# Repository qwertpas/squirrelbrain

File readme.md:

## Squirrelbrain v2

[Youtube video](https://youtube.com/shorts/pgTb6q6fkRE?feature=shared)

Main control board for the [Pintobotics](https://pintobotics.substack.com) robotic squirrel. It uses a Seeeduino XIAO ESP32S3 for wireless communication with a base station, is able to drive [dynamixel 5V TTL servos](https://www.robotis.us/dynamixel-xl330-m077-t/) up to 6A, and has two separate RS485 buses. 

The RS485 buses are intended for:
* [Ø32controller](https://github.com/qwertpas/O32controller), a miniature closed-loop brushless motor driver
* [Ø12encoder](https://github.com/qwertpas/O12encoder), a miniature magnetic encoder (MA702)
* [Ø12imu](https://github.com/qwertpas/O12imu), a miniature IMU with built-in sensor fusion for orientation (LSM6DSV) 

Squirrelbrain has two load switches to allow the ESP32 to cut off power to the motors when the battery is still connected. One load switch operates an XT30 output, featuring current sensing and a programmed current limit of 38A (limit can be adjusted by replacing a resistor). The other load switch operates on the 5V supply intended for dynamixel servos.

Size: 27mm x 27mm

Mounting: 4x M2 on 32mm diameter circle 

Connections:
* 2x JST-SH 2pin connectors for RS485 communication (1 for each bus)
* 2x 4pin 0.5mm pitch double-sided FFC connectors for RS485 communication (1 for each bus)
* 2x solder pads for 3.3V output
* JST-EH 3pin connector for dynamixel TTL
* USB-C on the ESP32S3
* Optional camera module on the ESP32S3
* XT30U-M power in (5-15V)
* XT30U-F power out
* 4pin header for current sense output, extra GPIO, and 5V/GND output

#### Changelog from Squirrelbrain v1:
Squirrelbrain v1 does not have the FFC connectors and is missing a pullup on the dynamixel data line.

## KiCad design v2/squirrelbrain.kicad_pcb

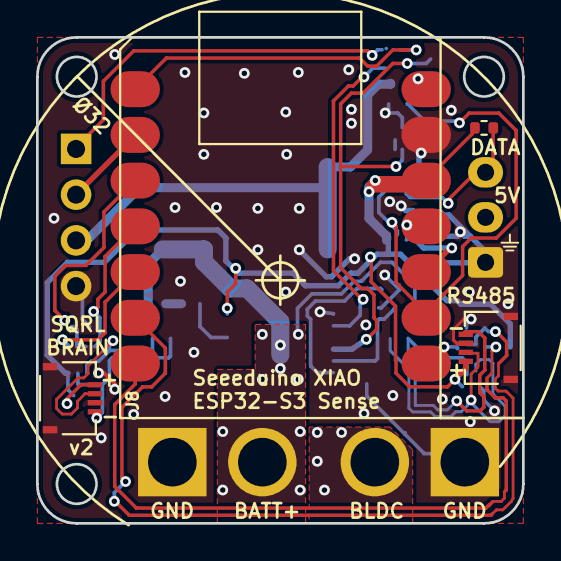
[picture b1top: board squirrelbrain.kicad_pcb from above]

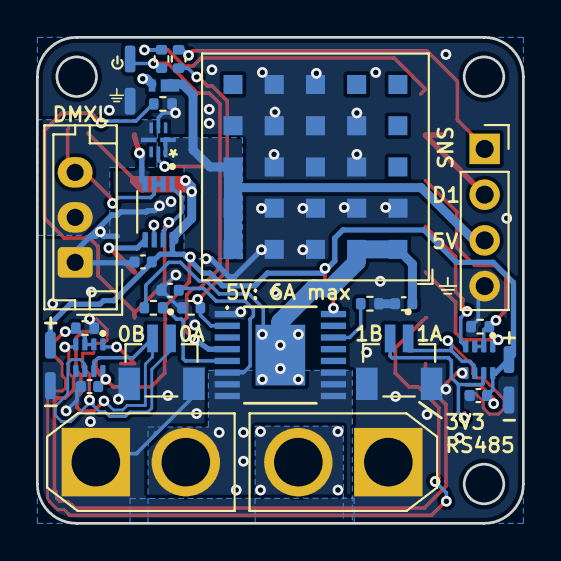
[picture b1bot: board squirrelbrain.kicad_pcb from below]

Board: 2 copper layers, 27.0 x 27.0 mm, 36 parts (32 on the bottom side), 28 nets.

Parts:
C1, C2, C3, C4, C5: 100nF; C_0402_1005Metric
D1: SDM2U30CSP; SDM2U30CSP-7
J1, J3: BM02B-SRSS-TB_LF__SN_; JST_BM02B-SRSS-TB_LF__SN_
J2: Conn_01x03; JST_EH_B3B-EH-A_1x03_P2.50mm_Vertical
J4: BATT; AMASS_XT30U-M_1x02_P5.0mm_Vertical
J5: BLDC_PWR; AMASS_XT30U-F_1x02_P5.0mm_Vertical
J6: GPIO1; PinSocket_1x04_P2.54mm_Vertical
J7, J8: Conn_01x04; TE_2328702-4
R1: 390R; R_0402_1005Metric
R2, R3, R4, R5, R6, R7, R8: 10k; R_0402_1005Metric
R9: 1k; R_0402_1005Metric
TP1, TP2, TP3, TP4, TP5, TP6: TestPoint; TestPoint_Pad_Rect
U1: RPM5.0-6.0; Converter_DCDC_RECOM_RPMx.x-x.0
U2: TPS1HB08BQPWPRQ1; TPS1HB08
U3: TPS22992SRXNR; TPS22992S
U4: SEEEDUINO-XIAO-ESP32S3; XIAO-ESP32S3-2.54-21X17.8MM
U5, U7: THVD1420DRLR; THVD1420DRLR_SOT-585
U6: SN74LVC2G241DCUR; SN74LVC2G125DCU

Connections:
+3V3: C3.1, C4.1, C5.1, J7.4, J8.4, R4.2, TP2.1, TP4.1, U2.16 (DIA_EN), U4.12 (3V3), U5.8 (VCC), U6.8 (VCC), U7.8 (VCC)
+5V: D1.2 (A), J6.3, U1.A5 (+VOUT), U1.B5 (+VOUT), U1.C5 (Sense), U3.1 (VBIAS), U3.2 (VIN)
+5VP: J2.2, U3.5 (QOD), U3.6 (VOUT)
+BATT: C1.1, J4.2, R3.2, U1.A1 (+VIN), U1.A2 (+VIN), U2.EPAD (VBB)
/5V_ESP: D1.1 (K), U4.14 (5V)
/BLDC_PWR: C2.1, J5.2, U2.6 (VOUT), U2.7 (VOUT), U2.8 (VOUT), U2.9 (VOUT), U2.10 (VOUT), U2.11 (VOUT)
/DMXL_DATA: J2.3, R4.1, U6.2 (1A), U6.3 (2Y)
/GPIO1: J6.2, U4.2 (PA4_A1_D1)
/MOTOR_ON: R9.1, TP1.1, U2.4 (EN), U3.8 (ON)
/MOTOR_ON_IO: R9.2, U4.1 (PA02_A0_D0)
/RS485_0A: J1.1, J7.3, U5.6 (A)
/RS485_0B: J1.2, J7.1, U5.7 (B)
/RS485_1A: J3.1, J8.3, U7.6 (A)
/RS485_1B: J3.2, J8.1, U7.7 (B)
/SNS: R1.2, R8.1, U2.2 (SNS)
/SNS_IO: J6.1, R8.2
/UART0_DE: R5.2, U4.6 (PA9_A5_D5_SCL), U5.2 (~RE), U5.3 (DE)
/UART0_RX: U4.8 (PB09_D7_RX), U5.1 (R)
/UART0_TX: U4.7 (PB08_A6_TX), U5.4 (D)
/UART1_DE: R7.2, U4.3 (PA10_A2_D2), U7.2 (~RE), U7.3 (DE)
/UART1_RX: U4.5 (PA8_A4_D4_SDA), U7.1 (R)
/UART1_TX: U4.4 (PA11_A3_D3), U7.4 (D)
/UART2_DE: R6.2, U4.9 (PA7_A8_D8_SCK), U6.1 (~1OE), U6.7 (~2OE)
/UART2_RX: U4.11 (PA6_A10_D10_MOSI), U6.6 (1Y)
/UART2_TX: U4.10 (PA5_A9_D9_MISO), U6.5 (2A)
GND: C1.2, C2.2, C3.2, C4.2, C5.2, J1.S1 (SHIELD), J1.S2 (SHIELD), J2.1, J3.S1 (SHIELD), J3.S2 (SHIELD), J4.1, J5.1, J6.4, J7.2, J7.MP (MountPin), J8.2, J8.MP (MountPin), R1.1, R2.1, R5.1, R6.1, R7.1, TP3.1, TP5.1, TP6.1, U1.A3 (GND), U1.A4 (GND), U1.B1 (GND), U1.B2 (GND), U1.B3 (GND), U1.B4 (GND), U1.C2 (GND), U1.C3 (GND), U1.C4 (GND), U1.D2 (GND), U1.D3 (GND), U1.D4 (GND), U1.D5 (GND), U1.E3 (GND), U1.E4 (GND), U2.1 (GND), U3.4 (GND), U4.13 (GND), U5.5 (GND), U6.4 (GND), U7.5 (GND)
unnamed: R3.1, U2.5 (ILIM)
unnamed: R2.2, U2.14 (SEL1)

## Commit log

2024-01-02 first commit, pick parts and pin mapping
2024-01-02 chose high side load switches
2024-01-02 add xt30, start routing
2024-01-02 finished routing? need to add 3v3 breakout
2024-01-03 rect test pads for 3v3
2024-01-03 generate gerbers
2024-02-13 add schematic labels just for reference
2024-03-11 readme, export pdf
2024-03-12 youtube video frame and smaller pics
2024-03-12 fix images
2024-04-15 Add MIT LICENSE
